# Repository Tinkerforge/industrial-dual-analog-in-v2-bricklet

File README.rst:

Industrial Dual Analog In Bricklet 2.0
======================================

This repository contains the firmware source code and the hardware design
files. The documentation generator configs can be found at
https://github.com/Tinkerforge/generators

Repository Content
------------------

software/:
 * examples/: Examples for all supported languages
 * build/: Compiled files
 * src/: Source code of firmware
 * Makefile: Makefile to build project

hardware/:
 * Contains KiCad project files and additionally schematics as PDF

datasheets/:
 * Contains datasheets for sensors and complex ICs that are used

Hardware
--------

The hardware is designed with the open source EDA Suite KiCad
(http://www.kicad.org). Before you are able to open the files,
you have to install the Tinkerforge kicad-libraries
(https://github.com/Tinkerforge/kicad-libraries). You can either clone
them directly in hardware/ or clone them in a separate folder and
symlink them into hardware/
(ln -s kicad_path/kicad-libraries project_path/hardware). After that you
can open the .pro file in hardware/ with KiCad and from there view and
modify the schematics and the PCB layout.

Software
--------

If you want to do your own Brick/Bricklet firmware development we highly
recommend that you use our build environment setup script and read the
tutorial (https://www.tinkerforge.com/en/doc/Tutorials/Tutorial_Build_Environment/Tutorial.html).

To compile the C code we recommend you to install the newest GNU Arm Embedded
Toolchain (https://launchpad.net/gcc-arm-embedded/+download).
You also need to install bricklib2 (https://github.com/Tinkerforge/bricklib2).

You can either clone it directly in software/src/ or clone it in a
separate folder and symlink it into software/src/
(ln -s bricklib_path/bricklib2 project_path/software/src/). Finally make sure to
have CMake installed (http://www.cmake.org/cmake/resources/software.html).

After that you can build the firmware by invoking make in software/.
The firmware (.zbin) can then be found in software/build/ and uploaded
with brickv (click button "Flashing" on start screen).

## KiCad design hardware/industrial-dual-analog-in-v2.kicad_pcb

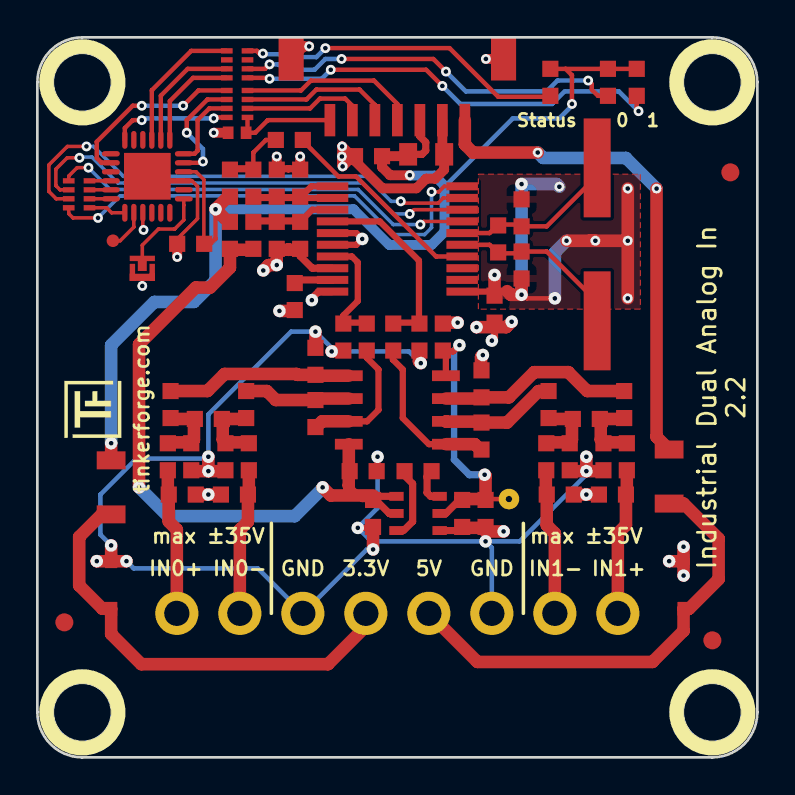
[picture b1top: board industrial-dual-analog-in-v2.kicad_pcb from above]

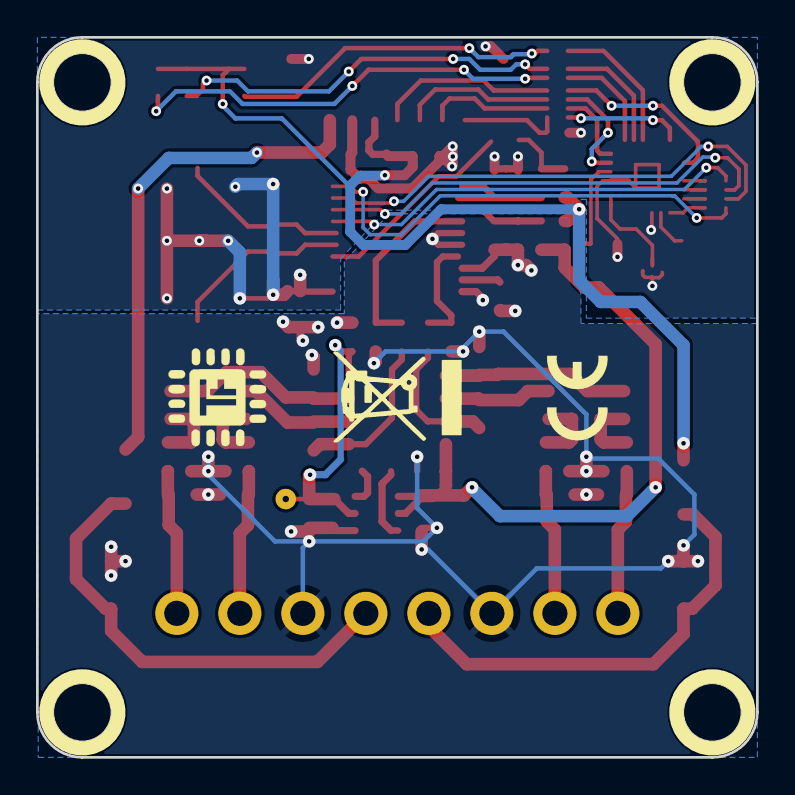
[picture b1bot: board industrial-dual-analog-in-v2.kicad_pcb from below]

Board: 2 copper layers, 40.0 x 40.0 mm, 79 parts (2 on the bottom side), 57 nets.

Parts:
C1, C2, C6, C12, C14, C15, C25: 100nF; C0603F
C3, C4, C5: 3.3µF; C0603F
C7: 10uF; C0805
C8, C9: 18pF; C0603F
C10, C11: 1nF; C0603F
C13, C16: 10µF; C0603F
C17, C19, C20, C22: 15pF; C0603F
C18, C21: 150pF; C0603F
C23: 220pF; C0402F
C24: 1uF; C0603F
D1: CDSOD323-T05SC; SOD-323
D2: CDSOD323-T03SC; SOD-323
D3, D4, D5: blue; D0603F
F1, F2: OZCJ0035FF2G; F1206
FB1, FB2: FILTER; C0603F
Fiducial_Mark: VAL**; Fiducial_Mark
Fiducial_Mark#2, Fiducial_Mark#3: VAL**; Fiducial_Mark
P1: CON-SENSOR2
P2: CONN_1; PINTST
P3: CONN_8; OQ_8P
P4: DEBUG; DEBUG_PAD
P5: DEBUG; SolderJumper
R1: 0; R0603F
R2: 1M; R0603F
R3, R21, R22, R23, R24: 100k; R0603F
R5, R6: 68.1; R0603F
R7, R12, R17, R18, R19, R20: 10; R0603F
R8, R9, R10, R11: 4k7/10ppm; R0603F
R13, R14, R15, R16: 280k/10ppm; R0603F
RP1, RP2: 82; 4X0402
RP3: 1k; 4X0402
U1: TLV272QDRQ1; SOIC8
U2: LM2664; SOT23-6
U3: XMC1100; QFN24-4x4mm-0.5mm
U4: MCP3911; SSOP20-53
U5, U6, U7, U8: DRILL; DRILL_NP
VAL: CE_5mm
VAL#2: WEEE_7mm
X1: 4MHz; HC49_US

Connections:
3V3: C7.1, C24.1, C25.2, D3.1, D4.1, D5.1, F2.1, FB1.2, FB2.2, P1.3, U3.10
+3.3VADC: C1.2, C3.1, FB1.1, R12.1, U1.8, U2.4, U2.5
+3.3VP: FB2.1, R3.1, R7.1
+5V: F1.1, P1.1
-VAA: C2.1, C4.1, C6.2, P2.1, U1.4, U2.2
ADC0: C10.2, R5.1, U4.7
ADC1: C11.2, R6.1, U4.4
AGND: C1.1, C2.2, C3.2, C4.2, C6.1, C10.1, C11.1, C14.1, C15.1, C16.1, C17.2, C19.1, C20.2, C22.1, D1.1, D2.1, P3.3, P3.6, R1.2, R10.1, R11.1, R21.2, R22.1, R23.2, R24.1, U2.1, U4.5, U4.6, U4.8, U4.10
DGND: C7.2, C8.1, C9.1, C12.1, C13.1, C23.2, C24.2, C25.1, P1.2, P1.EP, P5.1, R1.1, U3.3, U3.9, U3.EXP, U4.11
LED0: RP3.7, U3.14
LED1: RP3.8, U3.13
LEDS: RP3.5, U3.15
M-CLK: RP2.2, U4.18
M-CS: RP2.1, U4.17
M-MISO: RP2.3, U4.19
M-MOSI: RP2.4, U4.20
unnamed: C5.1, U2.6
unnamed: C5.2, U2.3
unnamed: C8.2, R2.1, U4.16, X1.1
unnamed: C9.2, R2.2, U4.15, X1.2
unnamed: C12.2, C13.2, R7.2, U4.1, U4.2
unnamed: C14.2, U4.9
unnamed: C15.2, C16.2, R12.2, U4.3
unnamed: C17.1, C18.2, R13.2, R17.1
unnamed: C18.1, C19.2, R14.2, R18.1
unnamed: C20.1, C21.2, R15.2, R19.1
unnamed: C21.1, C22.2, R16.2, R20.1
unnamed: C23.1, P1.7, RP1.1
unnamed: D1.2, F1.2, P3.5
unnamed: D2.2, F2.2, P3.4
unnamed: D3.2, RP3.4
unnamed: D4.2, RP3.1
unnamed: D5.2, RP3.2
unnamed: P1.4, RP1.4
unnamed: P1.5, RP1.3
unnamed: P1.6, RP1.2
unnamed: P3.1, R18.2, R22.2
unnamed: P3.2, R17.2, R21.1
unnamed: P3.7, R19.2, R23.1
unnamed: P3.8, R20.2, R24.2
unnamed: P4.1, U3.2
unnamed: P5.2, U3.7
unnamed: R3.2, U4.14
unnamed: R5.2, R8.1, U1.7
unnamed: R6.2, R9.1, U1.1
unnamed: R10.2, R14.1, U1.5
unnamed: R11.2, R16.1, U1.3
unnamed: R8.2, R13.1, U1.6
unnamed: R9.2, R15.1, U1.2
unnamed: RP2.6, U3.24
unnamed: RP2.7, U3.23
unnamed: RP2.8, U3.22
P0.2: RP2.5, U3.1
S-CLK: RP1.6, U3.11
S-CS: RP1.5, U3.20
S-MISO: RP1.8, U3.18
S-MOSI: RP1.7, U3.12

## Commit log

2018-02-22 Add datasheet
2018-02-22 Add schematic
2018-02-22 Add layout
2018-02-22 Fix routing
2018-02-23 Add .gitignore
2018-02-23 hardware: Remove special library
2018-03-13 Add correct logos and replace existing ones
2018-03-16 add status leds
2018-03-19 status text fixed
2018-05-11 Rename files
2018-05-18 Initial firmware commit
2018-06-06 fix origin, fix logos
2018-06-06 Adapt to bricklib2 callback-value changes to fix wrong threshold min/max type
2018-06-18 Change capacitor footprint(s) to C0402F
2018-06-28 Fix readme
2018-07-11 Add Makefile with docker support
2018-07-11 Update directory structure and build instructions
2018-07-11 Remove obsolete generate_makefile scripts
2018-07-17 specify processor
2018-07-18 Fixed unconnected GND via and reroute 3V3-wire next to "Status"-marking
2018-07-31 Add 3d models (*.FCStd & *.step)
2018-07-31 Add PDF schematic
2018-08-02 Firmware implementation
2018-08-03 Add examples
2018-09-14 vbnet: Fix typo in comment
2018-10-02 Add BOOTLOADER_FIX_POINTER_END define
2018-10-04 Add rev to changelog
2018-10-16 Remove in-development marker
2018-11-06 Add rust examples
2018-11-07 rust: Accept host names for ip connection, fix naming inconsistencies
2018-11-07 rust: Rename callback receivers.
2018-12-14 Add go examples.
2018-12-14 go: Fix printf parameters.
2018-12-18 go: Change import path.
2018-12-18 go: Change import path again.
2018-12-20 rust: Reformat examples.
2019-01-24 mqtt: Add examples.
2019-01-24 mqtt: Fix example header.
2019-01-24 mqtt: Remove executable bit in example permissions.
2019-01-24 go: Minor example fixes.
2019-01-24 mqtt: Minor example fixes.
2019-03-25 mqtt: Fix example whitespace.
2019-03-28 mqtt: Fix whitespace.
2019-05-29 Increase version for new release (changes in bricklib2)
2019-08-01 Fix error in sample rate configuration
    - Use coop task instead of complicated state machine
    - Properly reconfigure ADC in case of invalid data
2019-08-01 Add ref for version 2.0.2
2019-08-22 c: Adapt to bindings changes
2019-08-26 add version 2.1 with 4MHz Crystal
2019-08-26 ordered prototype
2019-08-28 fix logo positions
2019-09-02 add detection pin
2019-09-02 Simplify count/multiplier switch logic
    This saves a few bytes of flash (we need some bytes for new version
    discovery functionalty)
2019-09-02 Add hardware version discovery
    in 2.0 we use 10MHz oscillator, in 2.1 4MHz
2019-09-02 Set data rate by default on every startup
2019-09-02 Use different divisor MCLK divisor depending on oscillator
2019-09-02 Increase to version 2.0.3 and update changelog
2019-09-02 Add ref for 2.0.3
2019-09-03 Make sure to set "new-flag" to false as early as possible
    Otherwise it may be overwritten with true and afterwards erroneously
    set to false again
2019-09-03 Fix copy+paste error
2019-09-03 Change version to 2.0.4 and update changelog
2019-09-03 Add ref for 2.0.4
2020-01-13 examples: Use python3 input instead of python2 raw_input.
2020-01-13 examples: mqtt: Remove trailing whitespace.
2020-04-09 Fix callback handling.
    The old version handled only one voltage callback per callback tick.
    This in combination with the COMMUNICATION_CALLBACK_TICK_WAIT_MS of 1
    resulted in a maximum callback rate of 500 per second per channel.
2020-04-09 Fix callback handling fix.
2020-04-09 Update changelog and version
2020-04-09 Add commit ref to changelog
2020-04-28 Add all voltages callback.
2020-04-28 Implement some flash saving measures
2020-04-29 Move some struct members around to save a bit more of flash
2020-04-29 Use value has to change in all voltage callback.
2020-04-29 Implement more flash saving measures.
2020-04-30 Update version and changelog.
2020-04-30 Add commit ref to changelog.
2020-08-19 Add uc examples.
2020-08-25 uc: Fix whitespace
2020-08-27 uc: Fix warnings.
2020-08-31 uc: Use fixed-with placeholders in format strings.
2020-09-02 uc: Add example driver note.
2020-10-16 uc: Fix divisor type.
2021-10-25 Update KiCad link
    https://www.kicad.org/blog/2021/10/Avoid-links-to-former-kicad-domain/
2022-04-08 change opamp type
2022-04-08 increase version number
2022-04-19 examples: uc: Rename TF_HalContext to TF_HAL.
2022-04-27 uc: Adapt to bindings changes
2022-07-06 Add license files.
2022-12-12 Don't allow ADC value to start with 0x80, it indicates an error
2022-12-12 Add ref for 2.0.7
2023-01-26 Data Cleanup
2023-01-27 fix schematic
2025-10-04 Fix compatibility with new Docker build image (GCC 14.2.1)

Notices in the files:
hardware/industrial-dual-analog-in-v2.kicad_pcb:
Copyright (©) 2023, B.Nordmeyer
Copyright Tinkerforge GmbH 2019.
This documentation describes Open Hardware and is licensed under the
CERN OHL v. 1.1.
